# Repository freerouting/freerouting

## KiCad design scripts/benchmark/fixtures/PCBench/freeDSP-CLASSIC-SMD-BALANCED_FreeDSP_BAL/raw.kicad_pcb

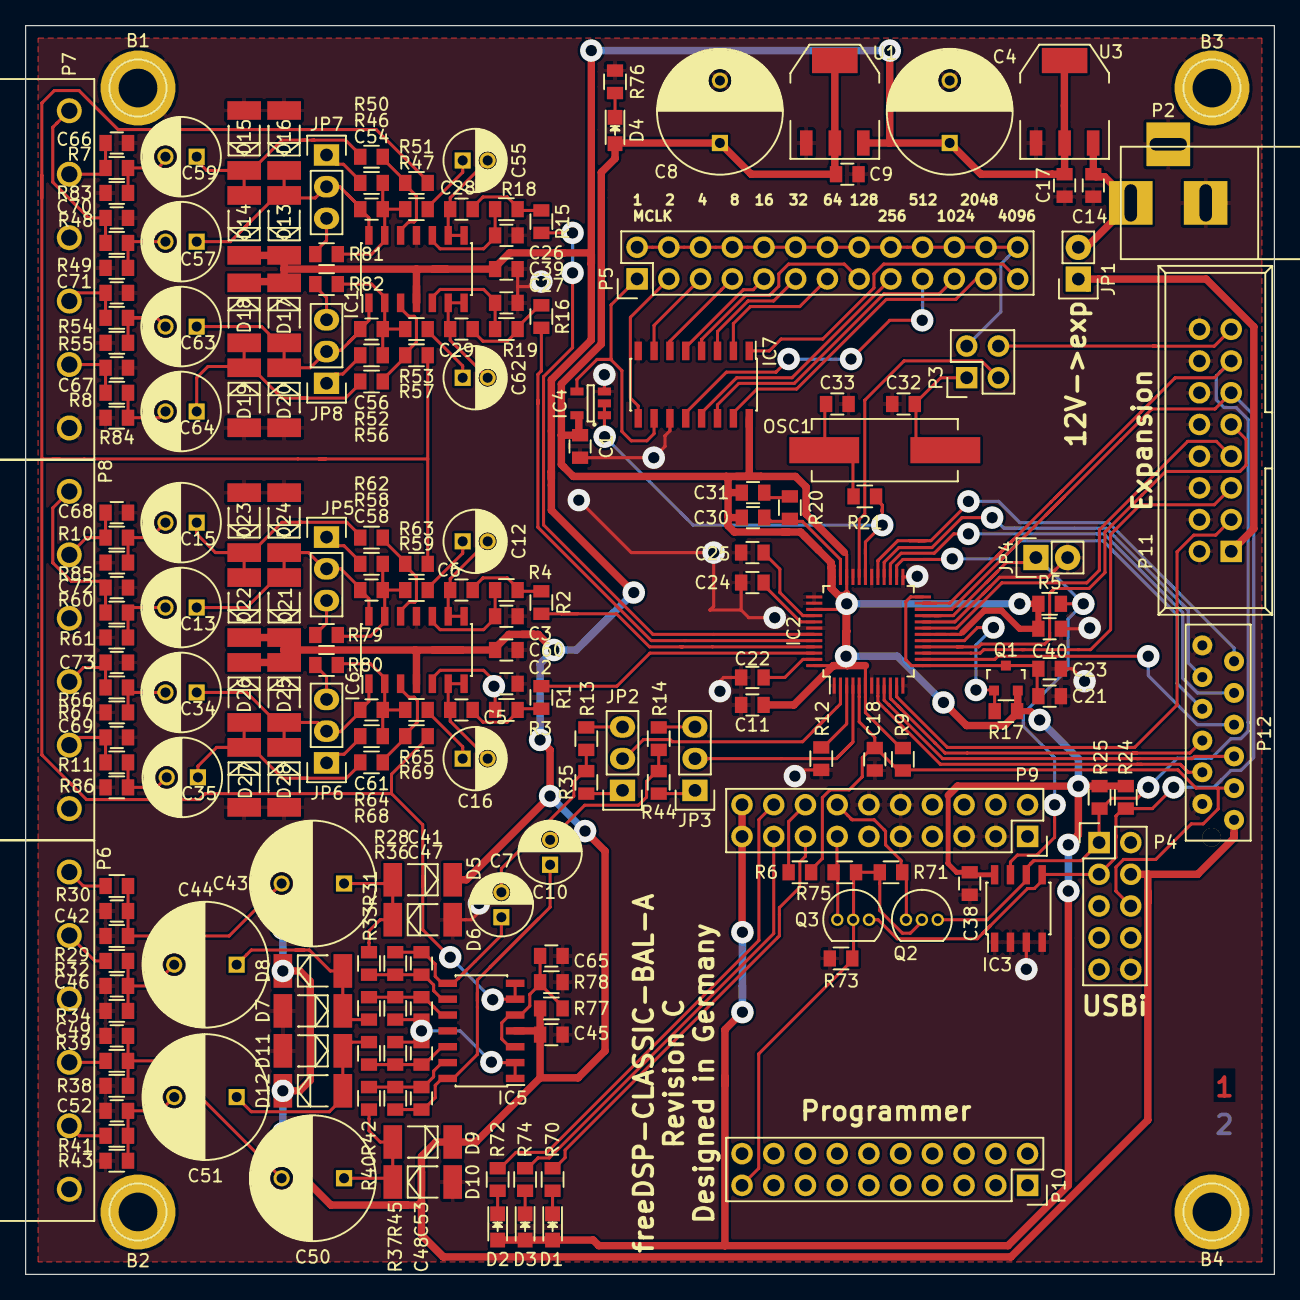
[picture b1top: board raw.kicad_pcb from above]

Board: 2 copper layers, 100.0 x 100.0 mm, 215 parts (0 on the bottom side), 148 nets.

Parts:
B1, B2, B3, B4: TEST_1P; 1pin
C1, C17, C23, C38, C39, C40, C45, C60: 100n; C0805-X7R
C2, C3, C26, C27: 150p; C0805-X7R
C4, C8: 220u./35V; C_Radial_D10_L13_P5
C5, C6, C28, C29: 470p; C0805-X7R
C7, C10, C12, C16, C55, C62: 100u./16V; C_Radial_D5_L11_P2
C9, C11, C14, C21, C22, C24, C25: 10u0; C0805-X7R
C13, C15, C34, C35, C57, C59, C63, C64: 47u0./50V; C_Radial_D6.3_L11.2_P2.5
C18: 10n0; C0805-X7R
C30: 3n30; C0805-X7R
C31: 56n0; C0805-X7R
C32, C33: 22p0; C0805-X7R
C41, C47, C48, C53: 27p0; C0805-X7R
C42, C46, C49, C52: 100p; C0805-X7R
C43, C44, C50, C51: 47u0./63V; C_Radial_D10_L16_P5
C54, C56, C58, C61: 47p0; C0805-X7R
C65: 22u0./X5R; C0805-X7R
C66, C67, C68, C69, C70, C71, C72, C73: 2n20; C0805-X7R
D1, D4: GREEN; LED_0805
D2, D3: RED; LED_0805
D5, D6, D7, D8, D9, D10, D11, D12, D13, D14, D15, D16, D17, D18, D19, D20, D21, D22, D23, D24, D25, D26, D27, D28: LL4002; MELF_Standard
IC1, IC5, IC6: AD8608ARZ; SOIC-14_3.9x8.7mm_Pitch1.27mm
IC2: ADAU1701; LQFP-48_7x7mm_Pitch0.5mm
IC3: 24AA256; SOIC-8_3.9x4.9mm_Pitch1.27mm
IC4: SN74LVC1G08DBVR; SOT-23-5
IC7: 74HC4040D; SOIC-16_3.9x9.9mm_Pitch1.27mm
JP1, JP4: JUMPER; Pin_Header_Straight_1x02
JP2, JP3, JP5, JP6, JP7, JP8: JUMPER3; Pin_Header_Straight_1x03
OSC1: 24M576Hz; Crystal_HC49-SD_SMD
P2: BARREL_JACK
P3: CONN_02X02; Pin_Header_Straight_2x02
P4: USBi; Pin_Header_Straight_2x05
P5: CONN_02X13; Pin_Header_Straight_2x13
P6, P7, P8: CONN_01X06; SL_5.08HC-06-90
P9, P10: CONN_02X10; Socket_Strip_Straight_2x10
P11: IDC-16G; IDC_Header_Straight_16pins
P12: MM-12G
Q1: ZXTP25040DFHTA; SOT-23
Q2, Q3: 2N7000; TO-92_Inline_Narrow_Oval
R1, R2, R3, R4, R15, R16, R18, R19: 4K75; C0805-RES
R5, R24, R25, R28, R36, R37, R45, R47, R53, R59, R65, R71, R75: 10K0; C0805-RES
R6, R20, R70, R72, R74, R76: 470R; C0805-RES
R7, R8, R10, R11, R48, R54, R60, R66: 56R0; C0805-RES
R9, R12: 18K0; C0805-RES
R13, R14: 9K09; C0805-RES
R17: 1K00; C0805-RES
R21, R30, R32, R39, R41: 100R; C0805-RES
R29, R34, R38, R43, R83, R84, R85, R86: 100K; C0805-RES
R31, R33, R40, R42: 14K0; C0805-RES
R35, R44: 261R; C0805-RES
R46, R52, R58, R64: 3K57; C0805-RES
R49, R55, R61, R67: 22K0; C0805-RES
R50, R51, R56, R57, R62, R63, R68, R69: 27R0; C0805-RES
R73: 1M00; C0805-RES
R77, R78: 47K0; C0805-RES
R79, R80, R81, R82: 17K4; C0805-RES
U1: 78033; SOT-223_Reg_MAE
U3: 7805; SOT-223_Reg_MAE

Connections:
3V3: C1.1, C8.1, C9.1, C11.1, C30.1, C31.1, C38.1, C40.1, D1.2, D2.2, D3.2, D4.2, IC2.6, IC2.18, IC2.34, IC2.36, IC2.39, IC2.48, IC3.8, IC4.5, IC7.16, P9.19, P9.20, Q1.2, R5.2, R9.2, R17.2, R24.2, R25.2, U1.VO
+5V: C4.1, C17.1, C39.2, C45.2, C60.2, D5.1, D8.1, D9.1, D12.1, D13.1, D14.1, D17.1, D18.1, D21.1, D22.1, D25.1, D26.1, IC1.4, IC5.4, IC6.4, P4.4, P12.1, R77.1, U1.VI, U3.VO
/DAC1: IC2.46, R1.2
/DAC2: IC2.45, R2.2
/DAC3: IC2.44, R16.2
/DAC4: IC2.43, R15.2
/IN1: IC2.2, JP2.2
/IN1+: P6.1, R30.2
/IN1-: P6.2, R32.2
/IN2: IC2.4, JP3.2
/IN2+: P6.4, R39.2
/IN2-: P6.5, R41.2
/OUT1+: C70.2, P7.1, R48.1
/OUT1-: C66.1, P7.2, R7.1
/OUT2+: C71.2, P7.4, R54.1
/OUT2-: C67.1, P7.5, R8.1
/OUT3+: C72.2, P8.1, R60.1
/OUT3-: C68.1, P8.2, R10.1
/OUT4+: C73.2, P8.4, R66.1
/OUT4-: C69.1, P8.5, R11.1
/USB_LED1: P9.15, R70.2
/USB_LED2: P9.18, R72.2
/USB_LED3: P9.17, R74.2
/USB_PWR_ON: P10.19, Q2.2, Q3.2, R71.2, R73.2, R75.1
/USB_SCL: P9.14, Q2.1, R71.1
/USB_SDA: P9.13, Q3.1, R75.2
/VO1: C47.2, C53.2, IC5.1, IC5.2, R36.2, R45.2
/VO2: IC5.6, IC5.7, R51.2, R57.2, R63.1, R69.2
/WP: IC2.21, IC3.7, JP4.1, R5.1
BCLK: IC2.19, P11.7
GND: B1.1, B2.1, B3.1, B4.1, C1.2, C2.1, C3.1, C4.2, C8.2, C9.2, C11.2, C14.2, C17.2, C18.2, C21.2, C22.2, C23.2, C24.2, C25.2, C26.1, C27.1, C32.2, C33.2, C38.2, C39.1, C40.2, C42.1, C45.1, C46.1, C49.1, C52.1, C60.1, C65.1, C66.2, C67.2, C68.2, C69.2, C70.1, C71.1, C72.1, C73.1, D6.2, D7.2, D10.2, D11.2, D15.2, D16.2, D19.2, D20.2, D23.2, D24.2, D27.2, D28.2, IC1.11, IC2.1, IC2.7, IC2.12, IC2.20, IC2.25, IC2.30, IC2.33, IC2.37, IC2.38, IC2.42, IC3.1, IC3.2, IC3.3, IC3.4, IC4.3, IC5.11, IC6.11, IC7.8, IC7.11, JP4.2, P2.2, P2.3, P4.10, P6.3, P6.6, P7.3, P7.6, P8.3, P8.6, P9.3, P9.5, P9.9, P9.10, P9.12, P11.2, P11.4, P11.6, P11.8, P11.10, P11.12, P11.14, P11.16, P12.2, P12.12, R12.1, R29.1, R34.1, R38.1, R43.1, R49.2, R55.2, R61.2, R67.2, R73.1, R76.2, R78.2, R83.2, R84.2, R85.2, R86.2, U1.GND, U3.GND
LRCLK: IC2.16, P11.9
MCLK: P3.4, P11.15
MDI: IC2.11, P11.3
MDO: IC2.15, P11.5
MP1: IC2.10, P12.6
MP2: IC2.29, P12.11
MP3: IC2.28, P12.10
MP4: IC2.8, P12.4
MP5: IC2.9, P12.5
MP7: IC2.14, P12.7
MP8: IC2.27, P12.9
MP9: IC2.26, P12.8
unnamed: C2.2, IC6.5, R3.1
unnamed: C3.2, IC6.10, R4.1
unnamed: C5.2, R1.1, R3.2
unnamed: C6.2, R2.1, R4.2
unnamed: C7.2, R13.1, R35.2
unnamed: C10.1, C48.1, IC5.14, R37.1
unnamed: C10.2, R14.1, R44.2
unnamed: C12.1, R59.2
unnamed: C6.1, C12.2, IC6.8, IC6.9
unnamed: C13.1, C58.1, D21.2, D24.1, IC6.14, JP5.2
unnamed: C13.2, R60.2, R61.1
unnamed: C15.1, D22.2, D23.1, R62.1
unnamed: C15.2, R10.2, R85.1
unnamed: C16.1, R65.2
unnamed: C5.1, C16.2, IC6.6, IC6.7
unnamed: C21.1, C23.1, IC2.13, IC2.24, Q1.3
unnamed: C22.1, IC2.47
unnamed: C24.1, IC2.41
unnamed: C25.1, IC2.40
unnamed: C26.2, IC1.10, R18.1
unnamed: C27.2, IC1.5, R19.1
unnamed: C28.1, C55.2, IC1.8, IC1.9
unnamed: C28.2, R15.1, R18.2
unnamed: C29.1, C62.2, IC1.6, IC1.7
unnamed: C29.2, R16.1, R19.2
unnamed: C30.2, IC2.35, R20.2
unnamed: C31.2, R20.1
unnamed: C32.1, OSC1.2, P3.1
unnamed: C33.1, OSC1.1, R21.2
unnamed: C34.1, C61.1, D25.2, D28.1, IC6.1, JP6.2
unnamed: C34.2, R66.2, R67.1
unnamed: C35.1, D26.2, D27.1, R68.1
unnamed: C35.2, R11.2, R86.1
unnamed: C7.1, C41.1, IC5.8, R28.1
unnamed: C41.2, IC5.9, R28.2, R31.1
unnamed: C42.2, C43.2, R29.2, R30.1
unnamed: C43.1, D5.2, D6.1, R31.2
unnamed: C44.1, D7.1, D8.2, R33.2
unnamed: C44.2, C46.2, R32.1, R34.2
unnamed: C47.1, IC5.10, R33.1, R36.1
unnamed: C48.2, IC5.13, R37.2, R40.1
unnamed: C49.2, C50.2, R38.2, R39.1
unnamed: C50.1, D9.2, D10.1, R40.2
unnamed: C51.1, D11.1, D12.2, R42.2
unnamed: C51.2, C52.2, R41.1, R43.2
unnamed: C53.1, IC5.12, R42.1, R45.1
unnamed: C54.1, C57.1, D13.2, D16.1, IC1.14, JP7.2
unnamed: C54.2, IC1.13, R46.2, R47.1, R81.2
unnamed: C55.1, R47.2
unnamed: C56.1, C63.1, D17.2, D20.1, IC1.1, JP8.2
unnamed: C56.2, IC1.2, R52.2, R53.1, R82.2
unnamed: C57.2, R48.2, R49.1
unnamed: C58.2, IC6.13, R58.2, R59.1, R79.2
unnamed: C59.1, D14.2, D15.1, R50.1
unnamed: C59.2, R7.2, R83.1
unnamed: C61.2, IC6.2, R64.2, R65.1, R80.2
unnamed: C62.1, R53.2
unnamed: C63.2, R54.2, R55.1
unnamed: C64.1, D18.2, D19.1, R56.1
unnamed: C64.2, R8.2, R84.1
unnamed: C65.2, IC5.3, IC5.5, R77.2, R78.1
unnamed: D1.1, R70.1
unnamed: D2.1, R72.1
unnamed: D3.1, R74.1
unnamed: D4.1, R76.1
unnamed: IC1.3, R56.2, R57.1
unnamed: IC1.12, R50.2, R51.1
unnamed: IC2.3, R12.2
unnamed: IC2.17, Q1.1, R17.1
unnamed: IC2.31, IC4.1, IC4.2, R21.1
unnamed: IC2.32, P3.3
unnamed: IC4.4, IC7.10, P5.1
unnamed: IC6.3, R68.2, R69.1
unnamed: IC6.12, R62.2, R63.2
unnamed: IC7.1, P5.25
unnamed: IC7.2, P5.13
unnamed: IC7.3, P5.11
unnamed: IC7.4, P5.15
unnamed: IC7.5, P5.9
unnamed: IC7.6, P5.7
unnamed: IC7.7, P5.5
unnamed: IC7.9, P5.3
unnamed: IC7.12, P5.19
unnamed: IC7.13, P5.17
unnamed: IC7.14, P5.21
unnamed: IC7.15, P5.23
unnamed: JP1.1, P11.1
unnamed: JP2.1, R35.1
unnamed: JP2.3, R13.2
unnamed: JP3.1, R44.1
unnamed: JP3.3, R14.2
unnamed: JP5.1, R58.1
unnamed: JP5.3, R79.1
unnamed: JP6.1, R64.1
unnamed: JP6.3, R80.1
unnamed: JP7.1, R46.1
unnamed: JP7.3, R81.1
unnamed: JP8.1, R52.1
unnamed: JP8.3, R82.1
unnamed: P3.2, P5.2, P5.4, P5.6, P5.8, P5.10, P5.12, P5.14, P5.16, P5.18, P5.20, P5.22, P5.24, P5.26
unnamed: P9.16, R6.1
SCL: IC2.23, IC3.6, P4.1, P11.13, Q2.3, R25.1
SDA: IC2.22, IC3.5, P4.3, P11.11, Q3.3, R24.1
VCC: C14.1, JP1.2, P2.1, U3.VI
_RESET: C18.1, IC2.5, P4.6, P12.3, R6.2, R9.1

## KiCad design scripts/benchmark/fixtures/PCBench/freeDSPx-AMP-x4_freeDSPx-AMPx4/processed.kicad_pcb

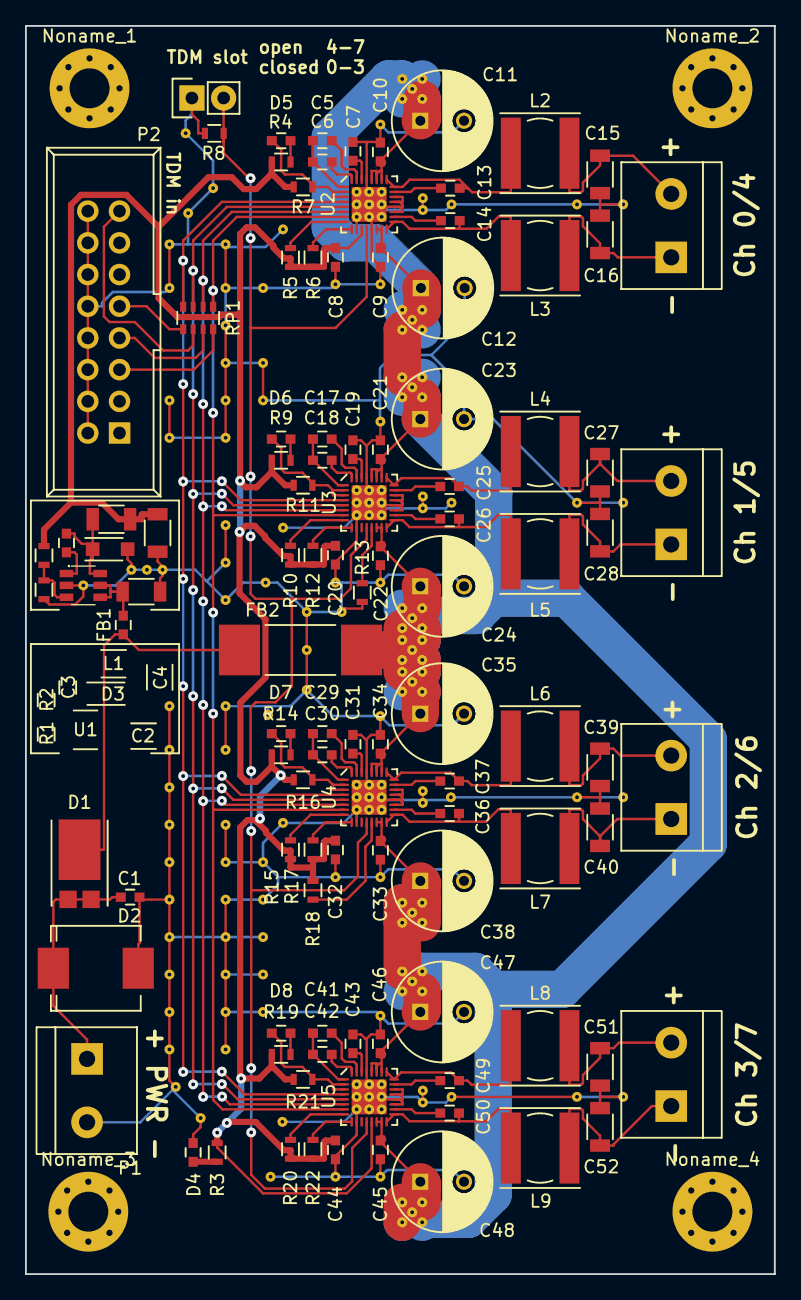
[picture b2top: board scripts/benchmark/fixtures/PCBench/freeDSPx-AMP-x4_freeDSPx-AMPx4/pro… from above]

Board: 2 copper layers, 60.0 x 100.0 mm, 283 parts (0 on the bottom side), 77 nets.

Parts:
C1, C3, C9, C10, C21, C22, C33, C34, C45, C46: 100n/50V; C_0603
C2: 10u/35V; C_1206
C4: 22u/10V; C_1206
C5, C6, C7, C8, C17, C18, C19, C20, C29, C30, C31, C32, C41, C42, C43, C44: 1u/16V; C_0603
C11, C12, C23, C24, C35, C36, C47, C48: 100u/35V; C_Radial_D8_L11.5_P3.5
C13, C14, C25, C26, C37, C38, C49, C50: 220n/25V; C_0603
C15, C16, C27, C28, C39, C40, C51, C52: 680n/50V; C_1206
D1: SBR10E45P5; PowerDI5
D2: 5.0SMDJ28CA; SMC
D3: PMEG6010ER; SOD-123W
D4, D5, D6, D7, D8: LED; C_0603
FB1: 470; C_0603
FB2: 115; C_3312
JP1: JUMPER; Pin_Header_Straight_1x02
L1: 47u; L_1207
L2, L3, L4, L5, L6, L7, L8, L9: 15u; Choke_SMD_6.0x6.0
Noname_1, Noname_2, Noname_3, Noname_4: MountingHole_3.2mm_M3_Pad_Via
None_1, None_2, None_3, None_4, None_5, None_6, None_7, None_8, None_9, None_10, None_11, None_12, None_13, None_14, None_15, None_16, None_17, None_18, None_19, None_20, None_21, None_22, None_23, None_24, None_25, None_26, None_27, None_28, None_29, None_30, None_31, None_32, None_33, None_34, None_35, None_36, None_37, None_38, None_39, None_40, None_41, None_42, None_43, None_44, None_45, None_46, None_47, None_48, None_49, None_50, None_51, None_52, None_53, None_54, None_55, None_56, None_57, None_58, None_59, None_60, None_61, None_62, None_63, None_64, None_65, None_66, None_67, None_68, None_69, None_70, None_71, None_72, None_73, None_74, None_75, None_76, None_77, None_78, None_79, None_80, None_81, None_82, None_83, None_84, None_85, None_86, None_87, None_88, None_89, None_90, None_91, None_92, None_93, None_94, None_95, None_96, None_97, None_98, None_99, None_100, None_101, None_102, None_103, None_104, None_105, None_106, None_107, None_108, None_109, None_110, None_111, None_112, None_113, None_114, None_115, None_116, None_117, None_118, None_119, None_120, None_121, None_122, None_123, None_124, None_125, None_126, None_127, None_128, None_129, None_130, None_131, None_132, None_133, None_134, None_135, None_136, None_137, None_138, None_139, None_140, None_141, None_142, None_143, None_144, None_145, None_146, None_147, None_148, None_149, None_150, None_151, None_152, None_153, None_154, None_155, None_156, None_157, None_158, None_159, None_160, None_161, None_162, None_163, None_164, None_165, None_166, None_167, None_168, None_169, None_170, None_171, None_172, None_173: Via_0.3mm_0.8mm
P1, P3, P4, P5, P6: CONN_01X02; RIACON101-2
P2: STDCONN; IDC_Header_Straight_16pins
R1: 1k2; R_0603
R2: 3k4; R_0603
R3, R4, R9, R14, R19: 620; R_0603
R5, R6, R10, R12, R15, R17, R20, R22: 2k4; R_0603
R7, R11, R16, R21: 100k; R_0603
R8, R13, R18: 22k; R_0603
RP1: 33; R_Array_Convex_4x0603
U1: LM2841X; SOT23-6_1.7x3.0mm_Pitch0.95mm
U2, U3, U4, U5: TAS5720M; VQFN-32_4x4mm_Pitch0.4mm

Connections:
+3V3: C4.2, C8.2, C20.2, C32.2, C44.2, L1.2, R2.1, R3.2, R4.1, R5.1, R6.1, R7.1, R9.1, R10.1, R11.1, R12.1, R14.1, R15.1, R16.1, R17.1, R18.2, R19.1, R20.1, R21.1, R22.1, U2.11, U5.13
ADRESS: JP1.2, R8.2, U2.12, U3.12, U4.12, U5.12
BCLK: RP1.2, U2.6, U3.6, U4.6, U5.6
GND: C1.1, C2.1, C4.1, C7.1, C8.1, C9.2, C10.2, C11.2, C12.2, C15.1, C16.1, C19.1, C20.1, C21.2, C22.2, C23.2, C24.2, C27.1, C28.1, C31.1, C32.1, C33.2, C34.2, C35.2, C36.2, C39.1, C40.1, C43.1, C44.1, C45.2, C46.2, C47.2, C48.2, C51.1, C52.1, D2.2, D3.2, D4.1, JP1.1, None_1.1, None_2.1, None_3.1, None_4.1, None_5.1, None_6.1, None_7.1, None_8.1, None_9.1, None_10.1, None_11.1, None_12.1, None_13.1, None_14.1, None_15.1, None_21.1, None_22.1, None_28.1, None_29.1, None_30.1, None_31.1, None_37.1, None_38.1, None_39.1, None_40.1, None_41.1, None_43.1, None_44.1, None_46.1, None_50.1, None_51.1, None_52.1, None_53.1, None_54.1, None_56.1, None_57.1, None_67.1, None_68.1, None_69.1, None_70.1, None_71.1, None_72.1, None_73.1, None_74.1, None_75.1, None_76.1, None_77.1, None_78.1, None_79.1, None_85.1, None_86.1, None_87.1, None_88.1, None_89.1, None_90.1, None_91.1, None_92.1, None_93.1, None_94.1, None_95.1, None_101.1, None_102.1, None_103.1, None_104.1, None_110.1, None_111.1, None_112.1, None_113.1, None_114.1, None_115.1, None_116.1, None_117.1, None_118.1, None_119.1, None_120.1, None_121.1, None_122.1, None_123.1, None_124.1, None_125.1, None_126.1, None_127.1, None_128.1, None_129.1, None_130.1, None_131.1, None_132.1, None_133.1, None_134.1, None_135.1, None_136.1, None_137.1, None_138.1, None_139.1, None_140.1, None_141.1, None_142.1, None_143.1, None_144.1, None_145.1, None_146.1, None_147.1, None_148.1, None_149.1, None_150.1, None_151.1, None_152.1, None_153.1, None_154.1, None_155.1, None_156.1, None_157.1, None_158.1, None_159.1, None_160.1, None_161.1, None_162.1, None_163.1, None_164.1, None_165.1, None_166.1, None_167.1, None_168.1, None_169.1, None_170.1, None_171.1, None_172.1, None_173.1, P1.2, P2.2, P2.4, P2.6, P2.8, P2.10, P2.12, P2.14, P2.16, R1.1, R8.1, R13.1, U1.2, U2.10, U2.13, U2.19, U2.20, U2.21, U2.22, U2.29, U2.33, U3.10, U3.19, U3.20, U3.21, U3.22, U3.29, U3.33, U4.10, U4.19, U4.20, U4.21, U4.22, U4.29, U4.33, U5.10, U5.19, U5.20, U5.21, U5.22, U5.29, U5.33
LRCLK: RP1.4, U2.4, U3.4, U4.4, U5.4
MCLK: RP1.3, U2.5, U3.5, U4.5, U5.5
unnamed: C1.2, D1.2, D2.1, P1.1
unnamed: C2.2, FB1.2, U1.4, U1.5
unnamed: C3.1, U1.1
unnamed: C3.2, D3.1, L1.1, U1.6
unnamed: C5.1, U2.31
unnamed: C5.2, C6.2, U2.1
unnamed: C6.1, U2.32
unnamed: C7.2, U2.30
unnamed: C13.1, U2.23
unnamed: C13.2, L2.1, U2.24, U2.25
unnamed: C14.1, L3.1, U2.16, U2.17
unnamed: C14.2, U2.18
unnamed: C15.2, L2.2, P3.2
unnamed: C16.2, L3.2, P3.1
unnamed: C17.1, U3.31
unnamed: C17.2, C18.2, U3.1
unnamed: C18.1, U3.32
unnamed: C19.2, U3.30
unnamed: C25.1, U3.23
unnamed: C25.2, L4.1, U3.24, U3.25
unnamed: C26.1, L5.1, U3.16, U3.17
unnamed: C26.2, U3.18
unnamed: C27.2, L4.2, P4.2
unnamed: C28.2, L5.2, P4.1
unnamed: C29.1, U4.31
unnamed: C29.2, C30.2, U4.1
unnamed: C30.1, U4.32
unnamed: C31.2, U4.30
unnamed: C37.1, U4.23
unnamed: C37.2, L6.1, U4.24, U4.25
unnamed: C38.1, L7.1, U4.16, U4.17
unnamed: C38.2, U4.18
unnamed: C39.2, L6.2, P5.2
unnamed: C40.2, L7.2, P5.1
unnamed: C41.1, U5.31
unnamed: C41.2, C42.2, U5.1
unnamed: C42.1, U5.32
unnamed: C43.2, U5.30
unnamed: C49.1, U5.23
unnamed: C49.2, L8.1, U5.24, U5.25
unnamed: C50.1, L9.1, U5.16, U5.17
unnamed: C50.2, U5.18
unnamed: C51.2, L8.2, P6.2
unnamed: C52.2, L9.2, P6.1
unnamed: D4.2, R3.1
unnamed: D5.1, R7.2, U2.2, U2.3
unnamed: D5.2, R4.2
unnamed: D6.1, R11.2, U3.2, U3.3
unnamed: D6.2, R9.2
unnamed: D7.1, R16.2, U4.2, U4.3
unnamed: D7.2, R14.2
unnamed: D8.1, R21.2, U5.2, U5.3
unnamed: D8.2, R19.2
unnamed: P2.5, RP1.8
unnamed: P2.7, RP1.7
unnamed: P2.9, RP1.5
unnamed: P2.15, RP1.6
unnamed: R1.2, R2.2, U1.3
unnamed: R5.2, U2.8
unnamed: R6.2, U2.9
unnamed: R10.2, U3.8
unnamed: R12.2, U3.9
unnamed: R13.2, U3.13
unnamed: R15.2, U4.8
unnamed: R17.2, U4.9
unnamed: R18.1, U4.13
unnamed: R20.2, U5.8
unnamed: R22.2, U5.9
SDATA: RP1.1, U2.7, U3.7, U4.7, U5.7
VCC: C9.1, C10.1, C11.1, C12.1, C21.1, C22.1, C23.1, C24.1, C33.1, C34.1, C35.1, C36.1, C45.1, C46.1, C47.1, C48.1, FB2.2, None_16.1, None_17.1, None_18.1, None_19.1, None_20.1, None_23.1, None_24.1, None_25.1, None_26.1, None_27.1, None_32.1, None_33.1, None_34.1, None_35.1, None_36.1, None_42.1, None_45.1, None_47.1, None_48.1, None_49.1, None_55.1, None_58.1, None_59.1, None_60.1, None_61.1, None_62.1, None_63.1, None_64.1, None_65.1, None_66.1, None_80.1, None_81.1, None_82.1, None_83.1, None_84.1, None_96.1, None_97.1, None_98.1, None_99.1, None_100.1, None_105.1, None_106.1, None_107.1, None_108.1, None_109.1, U2.14, U2.15, U2.26, U2.27, U2.28, U3.14, U3.15, U3.26, U3.27, U3.28, U4.14, U4.15, U4.26, U4.27, U4.28, U5.14, U5.15, U5.26, U5.27, U5.28
VIN: D1.1, FB1.1, FB2.1

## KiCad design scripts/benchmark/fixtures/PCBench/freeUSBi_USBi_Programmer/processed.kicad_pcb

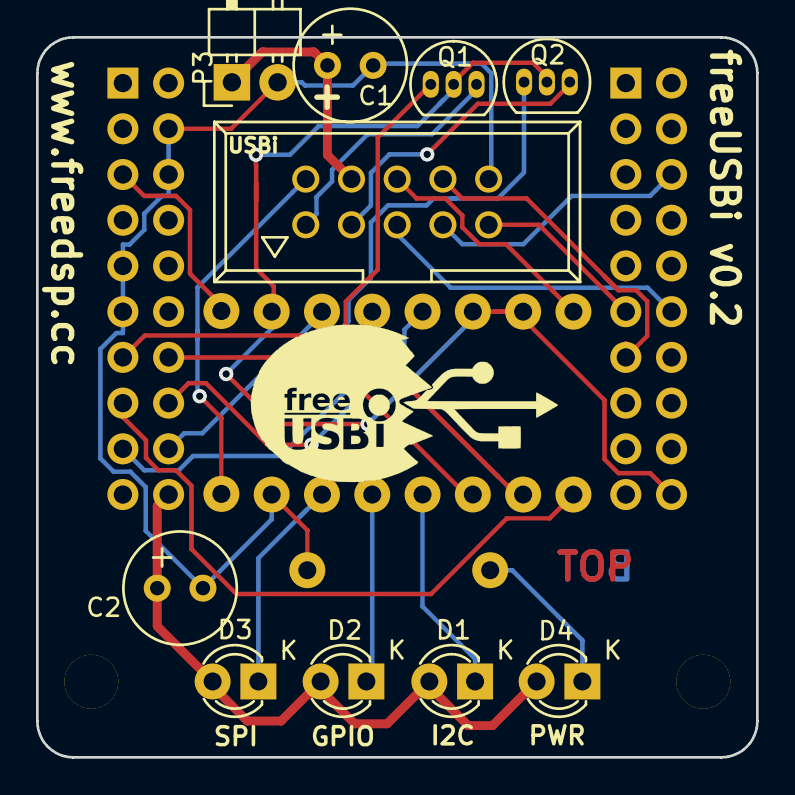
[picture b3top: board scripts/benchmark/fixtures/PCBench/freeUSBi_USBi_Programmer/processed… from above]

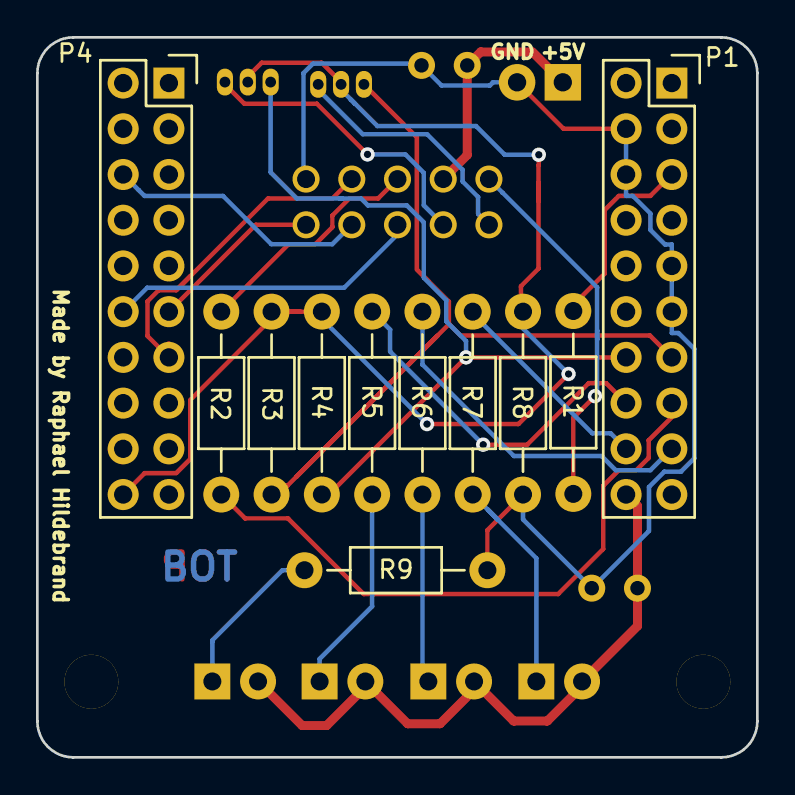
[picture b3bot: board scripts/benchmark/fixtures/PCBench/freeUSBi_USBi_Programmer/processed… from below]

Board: 2 copper layers, 40.0 x 40.0 mm, 21 parts (11 on the bottom side), 23 nets.

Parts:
C1, C2: 100u; Elko_vert_11.2x6.3mm_RM2.5_CopperClear
D1, D2, D3, D4: LED; LED-3MM
P1, P4: CONN_02X10; Socket_Strip_Straight_2x10
P2: CONN_02X05; VASCH5x2
P3: CONN_01X02; Pin_Header_Angled_1x02
Q1, Q2: Q_NMOS_DGS; TO-92_Inline_Narrow_Oval
R1: 49R9; Resistor_Horizontal_RM10mm
R2, R5, R6, R7, R9: 470R; Resistor_Horizontal_RM10mm
R3, R4: 10k; Resistor_Horizontal_RM10mm
R8: 1M; Resistor_Horizontal_RM10mm

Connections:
+3V3: C2.1, D1.2, D2.2, D3.2, D4.2, P1.20
+5VD: C1.1, P2.4, P3.1
BRD_~RESET: P2.6, R2.2
CCLK: P2.7, P4.6
CDATA: P2.8, P4.13
COUT: P2.5, P4.12
GND: C1.2, C2.2, P1.4, P1.6, P1.9, P1.11, P2.10, P3.2, R8.1, R9.2
LED_1: P1.16, R5.2
LED_2: P1.17, R6.2
LED_3: P1.18, R7.2
unnamed: D1.1, R5.1
unnamed: D2.1, R6.1
unnamed: D3.1, R7.1
unnamed: D4.1, R9.1
unnamed: P1.5, R1.1
unnamed: P1.15, R2.1
unnamed: P2.1, Q1.3
unnamed: P2.3, Q2.3
SCL: P1.13, Q1.1, R3.1
SDA: P1.14, Q2.1, R4.2
USB_CLK: P2.2, R1.2
USB_PWR_ON: P4.20, Q1.2, Q2.2, R3.2, R4.1, R8.2
~CLATCH1: P2.9, P4.11
